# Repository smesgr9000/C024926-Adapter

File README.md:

# C024926-Adapter

drop in replacement for Atari 7800 game ROMs DIP-28 for Atari C024926 or CO24926 PCBs. So if you game died but you want to reuse the original PCB to fix your cartridge.
The PCB will slot in the PINs on the PCB an can be used for 32kB-ROMs.

## Order PCB
To order the latest version either use KiCad or use release zip from GitHub.
To generate the Gerber files yourself, open _microcade.kicad_pcb_ in KiCad. Use _Fabrication Output_ > _Gerber_ and select an output folder and agree with _Plot_ with the default configruation. Also use _Fabrication Output_ > _Drill Files_ than select the same output folder and agree with _Generate Drill File_.

- enter length/width (36.4 x 18 mm)
- 2 layers
- 0.8mm thickness (my recommendation, other is possible too)
- FR4
- TG 150-160
- 6/6mil Min Tracking
- 0.3mm Hole Size
- Solder Mask - any is fine
- Silkscreen - any is fine
- No Edge Connector
- Finish - any is fine but would suggest HASL
- Tending Vias
- 1oz Finish Copper

Upload a zip containing the above generated files or use the release zip. Currently the price for 5 boards should be 5$.

## Progamm the EEPROM

Use your IC burner to program your dump back on the EPROM. Be aware to burn data without any headers. If you want to program the EEPROM after soldering set both Jumpers JP1 and 2 to "Prg" and wire your burner by crossing pin 1 and 27. See below:

Burner Pins | C024926-Adapter | header pin | C024926 pin description
--- | --- | --- | ---
27 | 1 | J1 1 | Write Enabled (WE)
2 | 2 | J1 2 | A12
3 | 3 | J1 3 | A7
4 | 4 | J1 4 | A6
5 | 5 | J1 5 | A5
6 | 6 | J1 6 | A4
7 | 7 | J1 7 | A3
8 | 8 | J1 8 | A2
9 | 9 | J1 9 | A1
10 | 10 | J1 10 | A0
11 | 11 | J1 11 | I/O0
12 | 12 | J1 12 | I/O1
13 | 13 | J1 13 | I/O2
14 | 14 | J1 14 | GND
15 | 15 | J2 14 | I/O3
16 | 16 | J2 13 | I/O4
17 | 17 | J2 12 | I/O5
18 | 18 | J2 11 | I/O6
19 | 19 | J2 10 | I/O7
20 | 20 | J2 9 | Chip Enabled (CE)
21 | 21 | J2 8 | A10
22 | 22 | J2 7 | Output Enabled (OE)
23 | 23 | J2 6 | A11
24 | 24 | J2 5 | A9
25 | 25 | J2 4 | A8
26 | 26 | J2 3 | A13
1 | 27 | J2 2 | A14
28 | 28 | J2 1 | VCC 

## Soldering

To finish the board two ICs and 2.54mm headers are required. Optional are two 1.27mm headers with shunts. This is needed if eeprom should be programmed soldered in.

Reference | Part | Amount | Description
--- | --- | --- | ---
U1 | Atmel/Microchip AT28C256-15SU | 1 | 256Kbit parallel EEPROM
U2 | Diodes 74AHCT1G04SE-7 | 1 | inverter SOT353
J1, J2 | Würth 61301411121 | 2 | 14pol 2.54mm header
JP1, JP2 | Sullins GRPB031VWVN-RC | 2 | optional, 3pol 1.27mm header
JP1, JP2 | Harwin M50-1900005 | 2 | optional, 1.27mm shunt

if jumper isn't used please bridge pin 1 and 2 "Use", see picture above.

## Jumper

- Use: Default, if the adapter is used in the cartridge
- Prg: If the EEPROM should be programmed see chapter "Programm the EEPROM"

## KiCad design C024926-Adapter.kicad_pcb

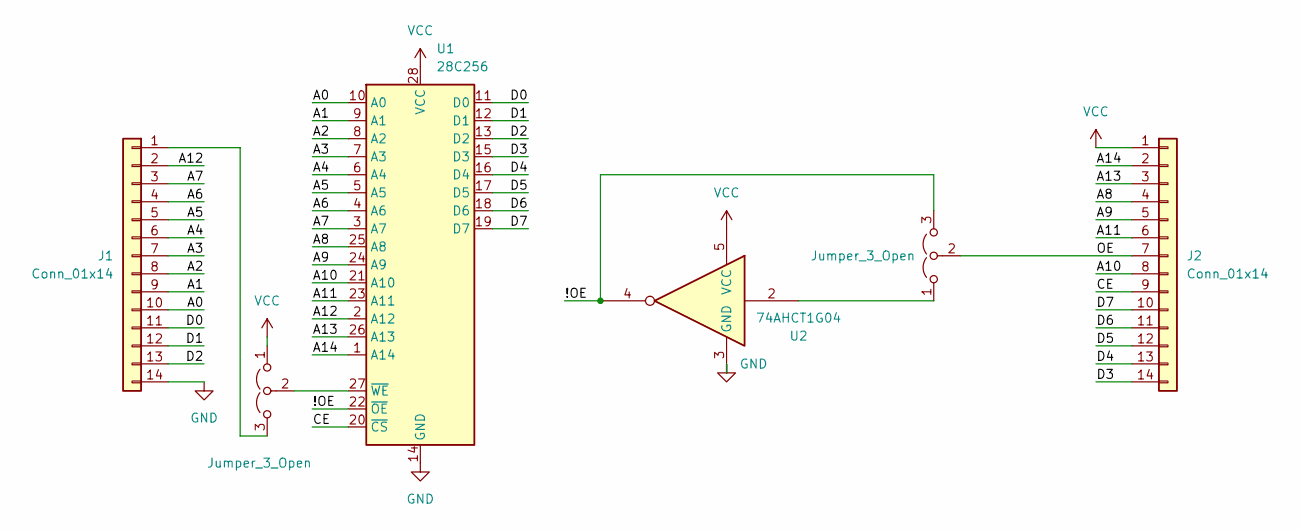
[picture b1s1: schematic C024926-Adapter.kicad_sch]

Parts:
J1, J2: Conn_01x14; PinHeader_1x14_P2.54mm_Vertical
JP1, JP2: Jumper_3_Open; PinHeader_1x03_P1.27mm_Vertical
U1: 28C256; SOIC-28W_7.5x17.9mm_P1.27mm
U2: 74AHCT1G04; SOT-353_SC-70-5_Handsoldering

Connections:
/!OE: JP1.3 (B), U1.22 (~OE), U2.4
/A0: J1.10, U1.10 (A0)
/A1: J1.9, U1.9 (A1)
/A2: J1.8, U1.8 (A2)
/A3: J1.7, U1.7 (A3)
/A4: J1.6, U1.6 (A4)
/A5: J1.5, U1.5 (A5)
/A6: J1.4, U1.4 (A6)
/A7: J1.3, U1.3 (A7)
/A8: J2.4, U1.25 (A8)
/A9: J2.5, U1.24 (A9)
/A10: J2.8, U1.21 (A10)
/A11: J2.6, U1.23 (A11)
/A12: J1.2, U1.2 (A12)
/A13: J2.3, U1.26 (A13)
/A14: J2.2, U1.1 (A14)
/CE: J2.9, U1.20 (~CS)
/D0: J1.11, U1.11 (D0)
/D1: J1.12, U1.12 (D1)
/D2: J1.13, U1.13 (D2)
/D3: J2.14, U1.15 (D3)
/D4: J2.13, U1.16 (D4)
/D5: J2.12, U1.17 (D5)
/D6: J2.11, U1.18 (D6)
/D7: J2.10, U1.19 (D7)
/OE: J2.7, JP1.2 (C)
GND: J1.14, U1.14 (GND), U2.3 (GND)
unnamed: J1.1, JP2.3 (B)
unnamed: JP1.1 (A), U2.2
unnamed: JP2.2 (C), U1.27 (~WE)
VCC: J2.1, JP2.1 (A), U1.28 (VCC), U2.5 (VCC)

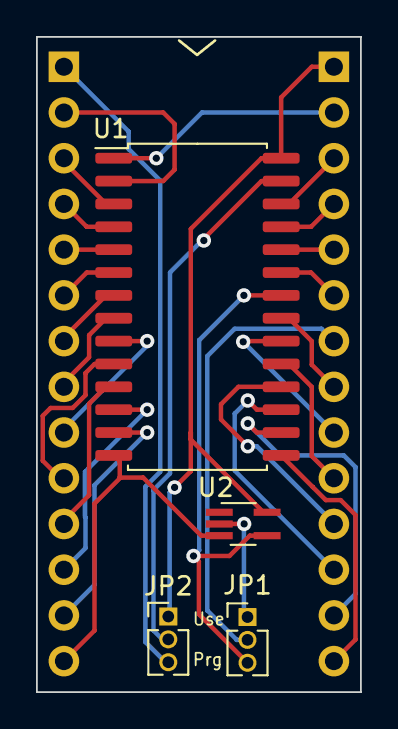
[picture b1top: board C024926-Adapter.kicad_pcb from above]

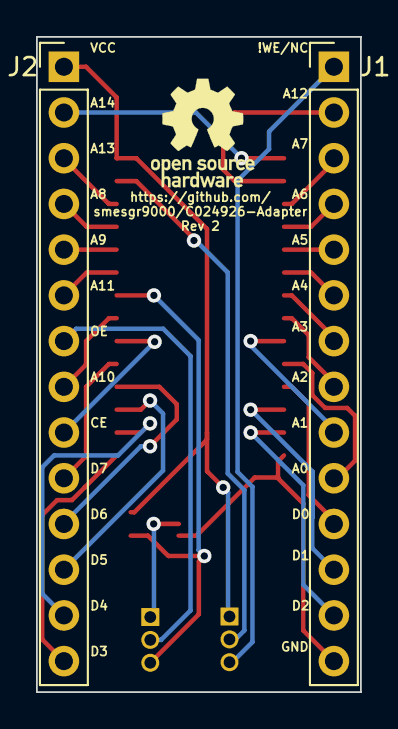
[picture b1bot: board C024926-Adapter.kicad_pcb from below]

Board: 2 copper layers, 18.0 x 36.4 mm, 6 parts (2 on the bottom side), 31 nets.

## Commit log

2024-04-07 inital GIT release
2024-04-07 add documentation
2024-04-07 fix image
2024-04-07 improve docu
2024-04-07 fix table
2024-04-09 fix link
2024-04-16 add LICENSE information
2024-12-20 update to Kicad 8
